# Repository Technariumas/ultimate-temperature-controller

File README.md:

# The Ultimate temperature controller
I've built a bunch of various temperature controllers and temperature sensor interfaces over the years. This one is to end the suffering. 

Features:
 * Arduino compatible
 * Thermocouple input via MAX31855
 * Output to LCD via I2C interface
 * Relay output
 * Open collector output
 * RS485 interface 
 * 4 key keypad interface
 * SD card

The device can act as a standalone controller or as a slave / master on RS485 network. 

## Standalone operation

Standalone controller is equiped with a LCD screen, a keypad and a SD card. Files containing temperature profiles can be stored on the SD card. A profile can be selected using the menu system via keypad and LCD interface. PID controller runs on the microcontroller and ensures the precise temperature control.

Power is controlled with a solid state relay. Open collector output is used to turn the SSR on and off. Alternatively an on-board mechanical relay can be used for power controll. 

Controller is powered by internal low power 12V SMPS.

## Slave operation

In slave mode no keypad and SD card is available, controller can be equiped with a more robust 7 segment LED screen for temperature readout. The slave controller sits on a RS485 network and listens for temperature commands from the master controller.

Slave has the same power output options as in standalone mode. 12V supply for the slave can be supplied by either a local SMPS or via UTP cable from the master. 

## Master operation

In case of master operation the master controller scans RS485 network for slaves. SD card is used to store temperature profiles. A profile can be selected via LCD/keypad interface for each of the slaves available on the RS485 network.

Master is not equiped with power switching options, but can provide 12V to slaves.

# The first prototype board

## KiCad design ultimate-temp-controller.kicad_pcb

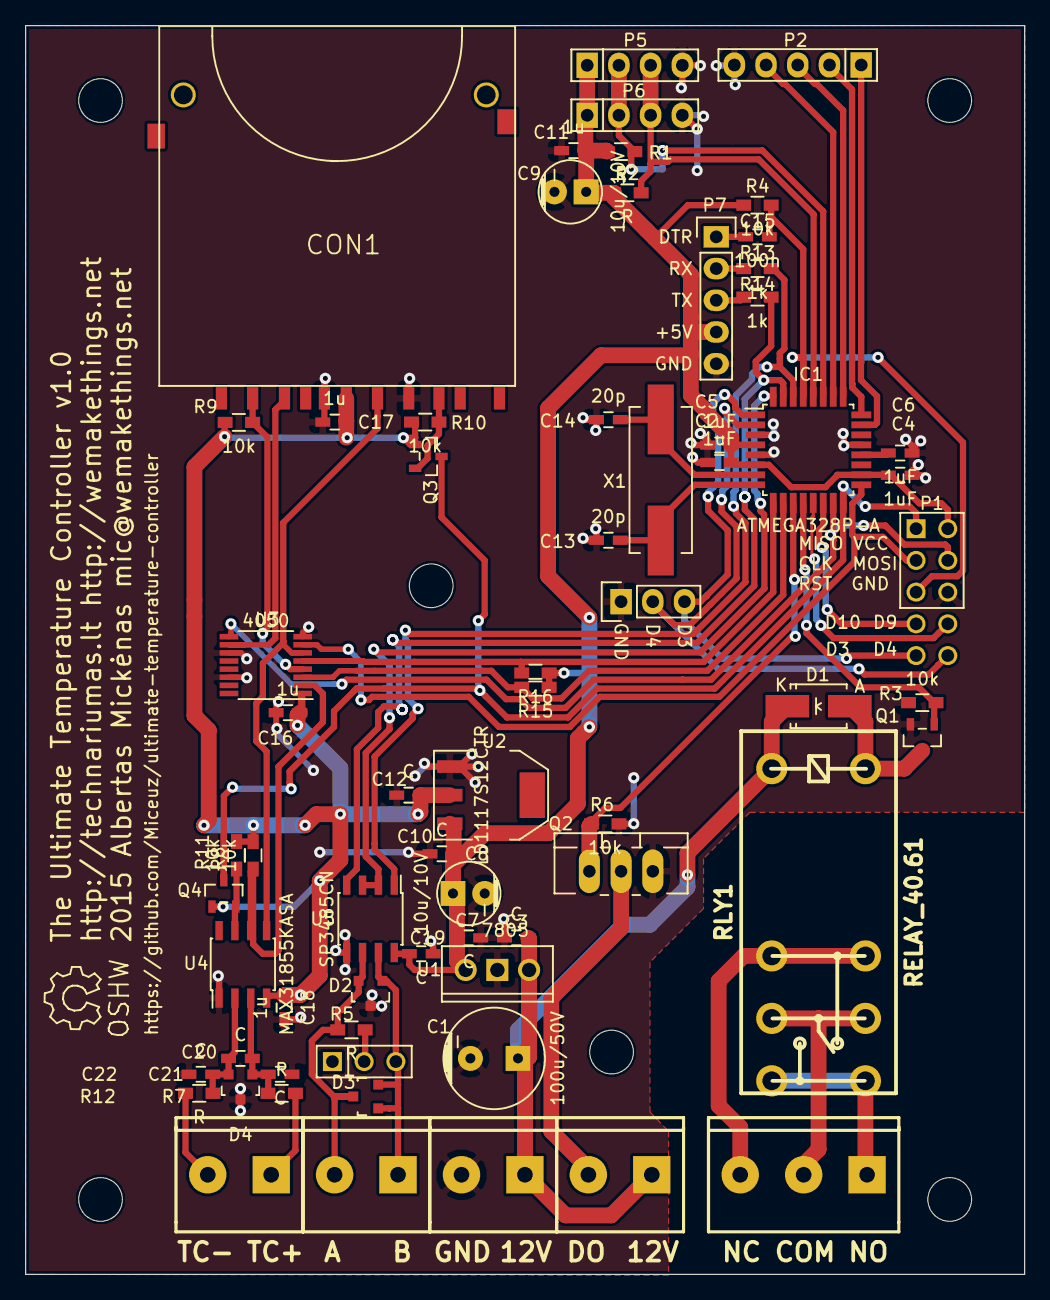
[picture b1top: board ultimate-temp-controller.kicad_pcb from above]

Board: 2 copper layers, 80.0 x 100.0 mm, 76 parts (0 on the bottom side), 49 nets.

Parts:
C1: 100u/50V; Capacitor8x13RM3.8
C2, C4, C5, C6: 1uF; C_0603_HandSoldering
C3, C7, C10, C12, C19, C20, C21, C22: C; C_0603_HandSoldering
C8, C9: 10u/10V; Capacitor5x6RM2.5
C11, C16, C17, C18: 1u; C_0603_HandSoldering
C13, C14: 20p; C_0603_HandSoldering
C15: 100n; C_0603_HandSoldering
CON1: SD_Card; SD-CARD-PROCON-19608
D1: DIODE; Diode-SMA_Handsoldering
D2, D3, D4: TVS-DUAL; SOT-23
IC1: ATMEGA328P-A; TQFP-32_7x7mm_Pitch0.8mm
JP1: TERM; pin_array_1x03
MountingHole_3-5mm, MountingHole_3-5mm#2, MountingHole_3-5mm#3, MountingHole_3-5mm#4, MountingHole_3-5mm#5, MountingHole_3-5mm#6: VAL**; MountingHole_3-5mm
P1: ISP; pin_array_2x03
P2: BUTTONS; Pin_Header_Straight_1x05
P3: OPEN_DRAIN; mors_2p
P4: POWER; mors_2p
P5: I2C1; Pin_Header_Straight_1x04
P6: I2C2; Pin_Header_Straight_1x04
P7: CONN_01X05; Pin_Header_Straight_1x05
P8: THERMOCOUPLE; mors_2p
P9: RELAY; mors_3p
P10: RS485; mors_2p
Pin_Header_Straight_1x02, Pin_Header_Straight_1x02#2: VAL**; Pin_Header_Straight_1x02
Pin_Header_Straight_1x03: VAL**; Pin_Header_Straight_1x03
Q1, Q3, Q4: MOS_N; sot23
Q2: MOS_N; TO-220_FET-GDS_Vertical_LargePads
R1, R2, R5, R7, R12: R; R_0603_HandSoldering
R3, R4, R6, R8, R9, R10, R11, R15, R16: 10k; R_0603_HandSoldering
R13, R14: 1k; R_0603_HandSoldering
RLY1: RELAY_40.61; relay_40.61
Symbol_OSHW-Logo_SilkScreen: VAL**; Symbol_OSHW-Logo_SilkScreen
U1: 7805; LM78XXV
U2: LD1117S12CTR; SOT-223
U3: 4050; TSSOP-16_4.4x5mm_Pitch0.65mm
U4: MAX31855KASA; SOIC-8_3.9x4.9mm_Pitch1.27mm
U5: SP3485CN; SOIC-8_3.9x4.9mm_Pitch1.27mm
X1: CRYSTAL; Crystal_HC49-SD_SMD

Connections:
+3V3: C12.1, C16.1, C17.1, C18.1, CON1.4, Q3.G, Q4.G, R8.1, R9.1, R10.1, R11.1, U2.2, U3.1, U4.4
+5V: C2.1, C4.1, C5.1, C7.1, C8.1, C9.1, C10.1, C11.1, C19.1, IC1.4, IC1.6, IC1.18, P1.2, P5.1, P6.1, P7.4, R1.1, R2.1, R4.1, R15.1, R16.1, U1.VO, U2.3, U5.8
+12V: C1.1, C3.1, D1.2, P3.1, P4.1, RLY1.2, U1.VI
/controller/BUTTON1: IC1.23, P2.1
/controller/BUTTON2: IC1.24, P2.2
/controller/BUTTON3: IC1.25, P2.3
/controller/BUTTON4: IC1.26, P2.4
/controller/CLK: IC1.17, P1.3, U3.7
/controller/CLK_3V3: CON1.5, U3.6, U4.5
/controller/CS_SD: IC1.9, R16.2, U3.5
/controller/CS_SD_3V3: CON1.1, R9.2, U3.4
/controller/CS_TC: IC1.10, R15.2, U3.3
/controller/CS_TC_3V3: R8.2, U3.2, U4.6
/controller/DRAIN: P3.2, Q2.D
/controller/DTR: C15.1, P7.1
/controller/MISO: IC1.16, P1.1, Q3.D, Q4.D
/controller/MOSI: IC1.15, P1.4, U3.9
/controller/MOSI_3V3: CON1.2, U3.10
/controller/RELAY_COM: P9.2, RLY1.11, RLY1.21
/controller/RELAY_NC: P9.3, RLY1.12, RLY1.22
/controller/RELAY_NO: P9.1, RLY1.14, RLY1.24
/controller/RELAY_ON: IC1.12, Q1.G, R3.1
/controller/RESET: C15.2, IC1.29, P1.5, R4.2
/controller/RS485A: D2.2, D3.3, P10.2, R5.1, U5.6
/controller/RS485B: D2.1, D3.1, D3.2, JP1.3, P10.1, U5.7
/controller/RS485DE: IC1.32, U5.2, U5.3
/controller/RX: P7.2, R13.1
/controller/RXD: IC1.30, R13.2, U5.1
/controller/SCL: IC1.28, P5.3, P6.3, R2.2
/controller/SDA: IC1.27, P5.2, P6.2, R1.2
/controller/TC+: P8.1, R7.1
/controller/TC-: P8.2, R12.1
/controller/TRANSISTOR_ON: IC1.11, Q2.G, R6.1
/controller/TX: P7.3, R14.1
/controller/TXD: IC1.31, R14.2, U5.4
GND: C1.2, C2.2, C3.2, C4.2, C5.2, C6.2, C7.2, C8.2, C9.2, C10.2, C11.2, C12.2, C13.2, C14.2, C16.2, C17.2, C18.2, C19.2, C21.2, C22.2, CON1.3, CON1.6, D2.3, D4.3, IC1.3, IC1.5, IC1.21, P1.6, P2.5, P4.2, P5.4, P6.4, P7.5, Pin_Header_Straight_1x03.1, Q1.S, Q2.S, R3.2, R6.2, U1.GND, U2.1, U3.8, U3.11, U3.14, U4.1, U5.5
unnamed: C6.1, IC1.20
unnamed: C13.1, IC1.8, X1.1
unnamed: C14.1, IC1.7, X1.2
unnamed: C20.1, C21.1, D4.1, R7.2, U4.3
unnamed: C20.2, C22.1, D4.2, R12.2, U4.2
unnamed: CON1.7, Q3.S, R10.2
unnamed: D1.1, Q1.D, RLY1.1
unnamed: IC1.1, Pin_Header_Straight_1x02.1, Pin_Header_Straight_1x03.3
unnamed: IC1.2, Pin_Header_Straight_1x02.2, Pin_Header_Straight_1x03.2
unnamed: IC1.13, Pin_Header_Straight_1x02#2.2
unnamed: IC1.14, Pin_Header_Straight_1x02#2.1
unnamed: JP1.2, R5.2
unnamed: Q4.S, R11.2, U4.7

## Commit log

2015-02-19 Initial. Schematics is kinda ready
2015-02-19 Add description
2015-02-19 Add ISP header
2015-02-19 Add annotations and netlist
2015-02-19 Add SVG drawing of schematics
2015-02-19 Add open drain output, shuffle other connectors around
2015-02-19 Shuffle stuff around, generate the new schematics svg
2015-02-19 Add netlist, assign footprints and 3d models, fool around with placement a bit
2015-02-22 Add the correct relay footprint, solve MISO voltage level conversion, route the PCB
2015-02-22 Create the correct SD card slot footprint for cheap and popular ebay SD card slot
2015-02-22 Shorten the board, reroute
2015-02-22 Make a better 3d render
2015-02-22 Remove ground fill for high voltage areas
2015-02-22 Add schematics svg
2015-02-23 Add dimensions
2015-02-23 Put silkscreen to order
2015-02-23 Add 3d render to readme
2015-02-23 Add description of three different operation modes.
2015-02-23 Add a serial header for Arduino compatible programming
2015-02-23 Break out leftover pins
2015-02-24 Add some silkscreen
2015-02-26 Use 4050 as a level shifter
2015-02-27 Turn 4050 180 degrees, enjoy better routing, move spare pins near ISP header
2015-02-27 Add mounting hole for expansion header, add a hole near screw terminals for more support
2015-02-27 add a new 3d image
2015-03-02 Add protection
2015-03-02 Add protection devices ot the PCB
2015-03-02 Consolidate spare pins on the expansion header
2015-03-30 Add a board photo
2015-03-30 Add gerbers
2015-03-30 Add comments about fixes for the next revision
2015-03-30 Add bom list:
2015-03-31 Fix schematics after kicad library upgrade
2015-03-31 Add more comments about what to fix
2015-04-04 Fix SD card footprint by mirroring the pads
2015-04-04 Fix SD card footprint by mirroring mechanical solder pads
2015-04-04 Optimise some tracks
2015-04-05 Fix missing ground connection. Change the MCU to Atmega328P for better Arduino compatibility
2015-04-05 Change TVS diode footprints to SOT-23
2015-04-05 Put netlist and fottprint assignments into order, but something went hugely wrong -- 3V3 net replaces VCC net. FML
2015-04-05 Fix netlist problem - update custom tuded ICs: U3 power connections are visible, U5 pin ordering more convenient. Saved cymbol changes to the local cache, not clear if this will help thoug..
2015-04-05 Swap TVS pins again. Add pullup resistors to CS lines.
